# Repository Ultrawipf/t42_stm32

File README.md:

## Tennis for two HD

This is a modern reproduction of ["Tennis for two"](https://de.wikipedia.org/wiki/Tennis_for_two) one of the first video games ever made.

The code is structured with a common part in the `Common` folder and chip specific subprojects.

### Variants
#### F303k-NUCLEO 
Designed for the official STM32F303k-Nucleo devboard for use in DIY and Breadboard builds.

Pinouts:
Signal | Pin
---|---
X-Out | A3 (PA4)
Y-Out | A4 (PA5)
Pot left | A0 (PA0)
Pot right | A1 (PA1)
Btn left | A5 (PA6)
Pot left | A6 (PA7)
LED right | D12 (PB4)
LED left | D13 (PB3)

#### F303CB
The latest all in one kit with optional potentiometers and connectors for controllers.

Designed for collections, museums and integrated setups.

The kit is available on [Lectronz](https://lectronz.com/products/LRAzdcngy_EcO1HJ9iuZsVuRM_s1uEzY95U8oW_G/preview).

#### L151
First version shown in the [Project video](https://www.youtube.com/watch?v=GjI3_GtFCSo).

Schematics are available in this repo.

### Links
* [Hackaday.io project blog](https://hackaday.io/project/203185-tennis-for-two-hd)
* [YouTube project video](https://www.youtube.com/watch?v=GjI3_GtFCSo)
* [Buy Tennis for two kits](https://lectronz.com/products/LRAzdcngy_EcO1HJ9iuZsVuRM_s1uEzY95U8oW_G/preview) (Custom builds possible. Contact me for details)

### Pictures
Click to watch YouTube video:

Breadboard setup F303k-NUCLEO

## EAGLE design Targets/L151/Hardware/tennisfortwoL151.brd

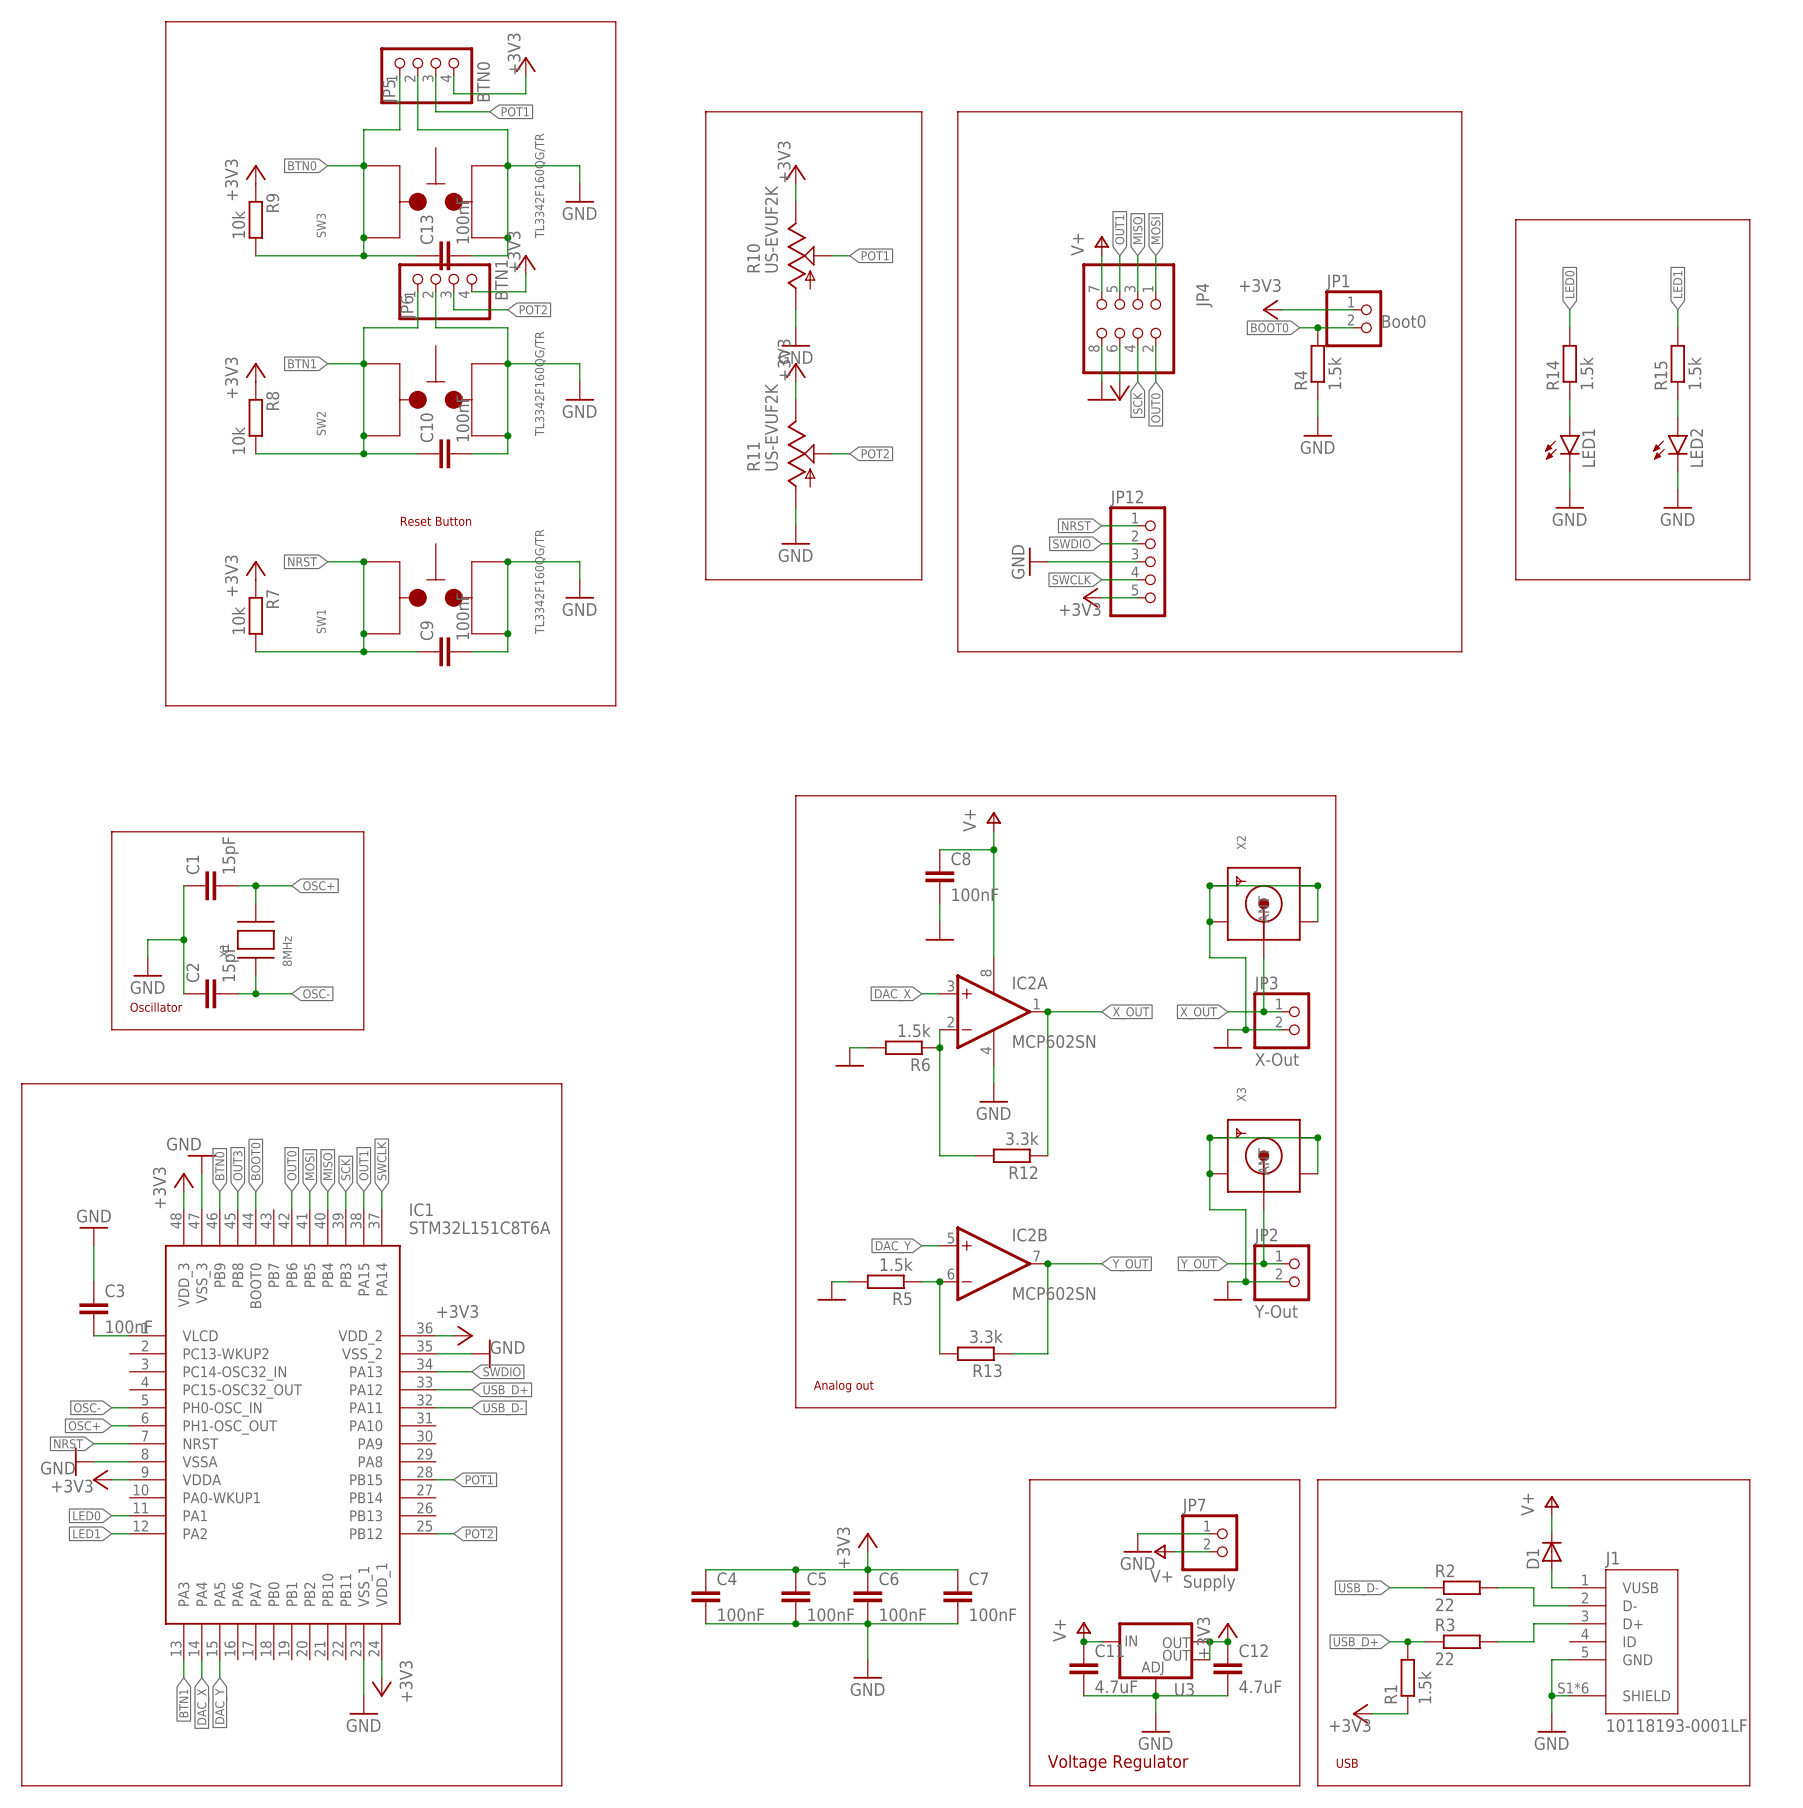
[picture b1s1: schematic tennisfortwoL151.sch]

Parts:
C1, C2: 15pF; C0603
C3, C4, C5, C6, C7, C8, C9, C10, C13: 100nF; C0603
C11, C12: 4.7uF; C0805
D1: DIODESMA; SMADIODE
IC1: STM32L151C8T6A; QFP50P900X900X160-48N
IC2: MCP602SN; SO08
J1: 10118193-0001LF; FCI_10118193-0001LF
JP1: Boot0; 1X02
JP2: Y-Out; 1X02
JP3: X-Out; 1X02
JP4: PINHD-2X4; 2X04
JP5: BTN0; 1X04/90
JP6: BTN1; 1X04/90
JP7: Supply; 1X02
JP12: PINHD-1X5; 1X05
LED1, LED2: LEDCHIPLED_0805; CHIPLED_0805
R1, R4, R5, R6, R14, R15: 1.5k; R0603
R2, R3: 22; R0603
R7, R8, R9: 10k; R0603
R10, R11: US-EVUF2K; EVUFXK
R12, R13: 3.3k; R0603
SW1, SW2, SW3: TL3342F160QG/TR
U3: V_REG_LM1117SOT223; SOT223
X1: 8MHz; NX5032
X2, X3: SMACONNECTOR_EDGE; SMA_EDGELAUNCH

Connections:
+3V3: C4.1, C5.1, C6.1, C7.1, C12.1, IC1.9 (VDDA), IC1.24 (VDD_1), IC1.36 (VDD_2), IC1.48 (VDD_3), JP1.1, JP4.6, JP5.4, JP6.4, JP12.5, R1.1, R7.1, R8.1, R9.1, R10.3 (E), R11.3 (E), U3.2 (OUT), U3.4 (OUT)
BOOT0: IC1.44 (BOOT0), JP1.2, R4.2
BTN0: C13.1, IC1.46 (PB9), JP5.1, R9.2, SW3.3, SW3.4
BTN1: C10.1, IC1.13 (PA3), JP6.1, R8.2, SW2.3, SW2.4
DAC_X: IC1.14 (PA4), IC2.3 (+IN)
DAC_Y: IC1.15 (PA5), IC2.5 (+IN)
GND: C1.1, C2.1, C3.1, C4.2, C5.2, C6.2, C7.2, C8.2, C9.2, C10.2, C11.2, C12.2, C13.2, IC1.8 (VSSA), IC1.23 (VSS_1), IC1.35 (VSS_2), IC1.47 (VSS_3), IC2.4 (V-), J1.5 (GND), J1.S1 (SHIELD), J1.S2 (SHIELD), J1.S3 (SHIELD), J1.S4 (SHIELD), J1.S5 (SHIELD), J1.S6 (SHIELD), JP2.2, JP3.2, JP4.8, JP5.2, JP6.2, JP7.1, JP12.3, LED1.C, LED2.C, R4.1, R5.2, R6.2, R10.1 (A), R11.1 (A), SW1.1, SW1.2, SW2.1, SW2.2, SW3.1, SW3.2, U3.1 (ADJ), X2.GND@1 (GND4), X2.GND@2 (GND3), X2.GND@3 (GND2), X2.GND@4 (GND1), X3.GND@1 (GND4), X3.GND@2 (GND3), X3.GND@3 (GND2), X3.GND@4 (GND1)
LED0: IC1.11 (PA1), R14.2
LED1: IC1.12 (PA2), R15.2
MISO: IC1.40 (PB4), JP4.3
MOSI: IC1.41 (PB5), JP4.1
unnamed: C3.2, IC1.1 (VLCD)
unnamed: D1.A, J1.1 (VUSB)
unnamed: LED1.A, R14.1
unnamed: LED2.A, R15.1
unnamed: J1.2 (D-), R2.2
unnamed: J1.3 (D+), R3.2
unnamed: IC2.2 (-IN), R6.1, R12.2
unnamed: IC2.6 (-IN), R5.1, R13.2
NRST: C9.1, IC1.7 (NRST), JP12.1, R7.2, SW1.3, SW1.4
OSC+: C1.2, IC1.6 (PH1-OSC_OUT), X1.P$2
OSC-: C2.2, IC1.5 (PH0-OSC_IN), X1.P$1
OUT0: IC1.42 (PB6), JP4.2
OUT1: IC1.38 (PA15), JP4.5
OUT3: IC1.45 (PB8)
POT1: IC1.28 (PB15), JP5.3, R10.2 (S)
POT2: IC1.25 (PB12), JP6.3, R11.2 (S)
SCK: IC1.39 (PB3), JP4.4
SWCLK: IC1.37 (PA14), JP12.4
SWDIO: IC1.34 (PA13), JP12.2
USB_D+: IC1.33 (PA12), R1.2, R3.1
USB_D-: IC1.32 (PA11), R2.1
V+: C8.1, C11.1, D1.C, IC2.8 (V+), JP4.7, JP7.2, U3.3 (IN)
X_OUT: IC2.1 (OUT), JP3.1, R12.1, X2.P (ANT)
Y_OUT: IC2.7 (OUT), JP2.1, R13.1, X3.P (ANT)

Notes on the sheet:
Oscillator
USB
Voltage Regulator
Reset Button
Analog out

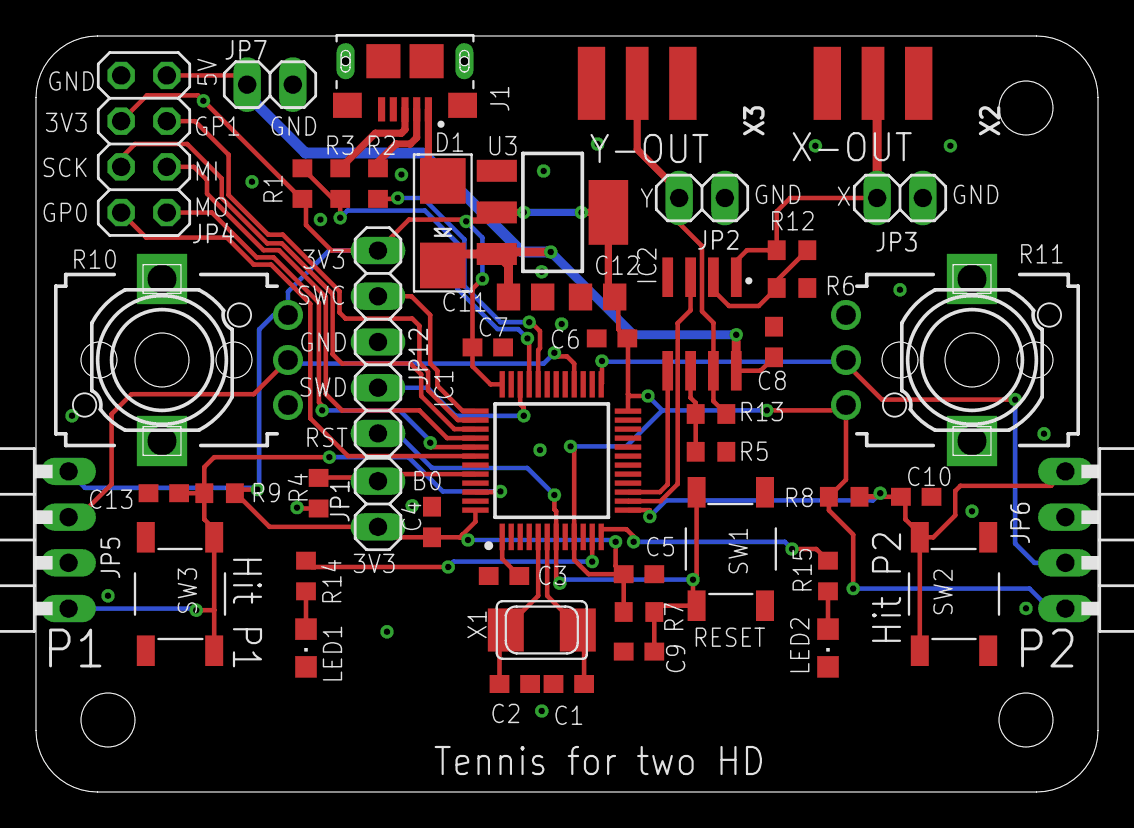
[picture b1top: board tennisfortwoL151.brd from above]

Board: 2 copper layers, 59.0 x 42.0 mm, 49 parts (0 on the bottom side), 34 nets.

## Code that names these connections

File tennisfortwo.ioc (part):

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Mcu.Name=STM32L151C(6-8-B)Tx
Mcu.Package=LQFP48
Mcu.UserName=STM32L151C8Tx
PA1.GPIOParameters=GPIO_Label
PA1.GPIO_Label=LED0
PA1.Signal=GPIO_Output
PA13.Mode=Serial_Wire
PA13.Signal=SYS_JTMS-SWDIO
PA14.Mode=Serial_Wire
PA14.Signal=SYS_JTCK-SWCLK
PA15.GPIOParameters=GPIO_Label
PA15.GPIO_Label=OUT1
PA15.Signal=GPIO_Output
PA2.GPIOParameters=GPIO_Label
PA2.GPIO_Label=LED1
PA2.Signal=GPIO_Output
PA3.GPIOParameters=GPIO_Label
PA3.GPIO_Label=BTN2
PA3.Signal=GPIO_Input
PA4.Signal=COMP_DAC1_group
PA5.Signal=COMP_DAC2_group
PB12.Mode=IN18
PB12.Signal=ADC_IN18
PB15.Mode=IN21
PB15.Signal=ADC_IN21
PB3.Mode=Full_Duplex_Master
PB3.Signal=SPI1_SCK
PB4.Mode=Full_Duplex_Master
PB4.Signal=SPI1_MISO
PB5.Mode=Full_Duplex_Master
PB5.Signal=SPI1_MOSI
PB6.GPIOParameters=GPIO_Label
PB6.GPIO_Label=OUT0
PB6.Signal=GPIO_Output
PB8.Signal=GPIO_Input
PB9.GPIOParameters=GPIO_Label
PB9.GPIO_Label=BTN1
PB9.Signal=GPIO_Input
PH0-OSC_IN.Mode=HSE-External-Oscillator
PH0-OSC_IN.Signal=RCC_OSC_IN
PH1-OSC_OUT.Mode=HSE-External-Oscillator
PH1-OSC_OUT.Signal=RCC_OSC_OUT
RCC.HSE_VALUE=8000000
RCC.SYSCLKFreq_VALUE=32000000
RCC.SYSCLKSource=RCC_SYSCLKSOURCE_PLLCLK
board=custom

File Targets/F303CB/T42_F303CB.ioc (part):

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Mcu.Name=STM32F303C(B-C)Tx
Mcu.Package=LQFP48
Mcu.UserName=STM32F303CBTx
PA1.GPIOParameters=GPIO_Label
PA1.GPIO_Label=LED0
PA1.Signal=GPIO_Output
PA11.Mode=Device
PA11.Signal=USB_DM
PA12.Mode=Device
PA12.Signal=USB_DP
PA13.Mode=Serial_Wire
PA13.Signal=SYS_JTMS-SWDIO
PA14.Mode=Serial_Wire
PA14.Signal=SYS_JTCK-SWCLK
PA2.GPIOParameters=GPIO_Label
PA2.GPIO_Label=LED1
PA2.Signal=GPIO_Output
PA3.GPIOParameters=GPIO_Label
PA3.GPIO_Label=BTN2
PA3.Signal=GPIO_Input
PA4.Signal=COMP_DAC1_group
PA5.Signal=COMP_DAC2_group
PB12.Mode=IN3-Single-Ended
PB12.Signal=ADC4_IN3
PB15.Mode=IN5-Single-Ended
PB15.Signal=ADC4_IN5
PB9.GPIOParameters=GPIO_Label
PB9.GPIO_Label=BTN1
PB9.Signal=GPIO_Input
PF0-OSC_IN.Mode=HSE-External-Oscillator
PF0-OSC_IN.Signal=RCC_OSC_IN
PF1-OSC_OUT.Mode=HSE-External-Oscillator
PF1-OSC_OUT.Signal=RCC_OSC_OUT
RCC.HSEPLLFreq_Value=8000000
RCC.HSE_VALUE=8000000
RCC.SYSCLKFreq_VALUE=72000000
RCC.SYSCLKSourceVirtual=RCC_SYSCLKSOURCE_PLLCLK
board=custom

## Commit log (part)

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2025-05-24 Physics tuning
2025-05-24 Trail tune
2025-05-25 Score logic & trail update
2025-05-25 Floor bounce score improved
2025-06-13 Set release to O1
2025-06-18 Prevent double bounce
2025-06-18 Immediately respawn after double bounce
2025-06-18 Added hardware folder
2025-06-20 Update timers for better stability
2025-06-24 Increased ball timeout, only active player triggers ball
2025-06-24 Create LICENSE
2025-06-24 Copyright notice update
2026-01-18 Restructured project
2026-01-18 Added F303k nucleo build
2026-01-18 L151 using tim6 for adc trigger
2026-01-18 Added slight dampening effect
2026-01-18 More accurate air resistance
2026-01-21 Reduce buffer glitches
2026-01-21 Increased ball trail resolution
2026-01-21 Speed+net tuning
2026-01-22 Refactored constants
2026-04-02 F303CB Target added
2026-04-08 Add hardware F303CB
2026-05-01 Add stm gitignore
2026-05-01 Update release settings
2026-05-01 Fix adc cal for L1
2026-05-01 Remove empty folder
2026-05-07 Update gitignore
2026-05-07 Changed F303CB timings
2026-06-03 Added printable case components

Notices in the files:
parts and their libraries:
SparkFun-IC-Power: Licensing: Creative Commons ShareAlike 4.0 International - https://creativecommons.org/licenses/by-sa/4.0
